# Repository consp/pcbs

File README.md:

This repository contains most of my public available PCB designs. Some are also in other repo's since they need software with them.

Available:

* SOJ32 <-> DIP32s adapter for SRAM chips
* MIDI Adapter for 15 pin gameport ports
* Adapter board for Sparta ION XGT motors

Not publicly available/on request:

* 3 PORT USB <-> CAN adapter compatible with custom linux socketcan kernel driver and modified SavvyCAN. https://github.com/consp/SavvyCAN
* Custom board for https://github.com/consp/ZigbeeP1

All stuff not already licenced otherwise (like forks) are only available under CC-BY-NC-4.0 https://creativecommons.org/licenses/by-nc/4.0/ . For commercial use contact me.

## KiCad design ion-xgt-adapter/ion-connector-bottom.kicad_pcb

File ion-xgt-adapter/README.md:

# Adapter for the (Sparta) ION XGT motors

The motor is a 20 pole, 24 slot PMSM. It should be able to function with hall sensors but due to how it's configured you need to make sure the hall sensors are very precicely aligned.
The top cover has a magnet ring which also has 20 magnet poles, we use that for hall sensors.

I forgot to take pictures before I sealed the motor again ... so no live images.

Features:
* WAGO 238-402 connector, which you can get from the original board
* Phoenix (or equivalen) 2.54mm screw terminals for the signal wires.
* Bottom and top traces for the phases since the cheap PCB manufacturers use 1oz copper you need as much as you can get, but it should be more than enough for the 24A max rating of the WAGO connectors.
* 0603 capacitor slots for when the s/n ratio is too much due to bad cable shielding, if you get a 15khz signal the phases are messing with the hall sensors. By putting a 1nF cap on all sensor lines you can get rid of some of the 15khz noise. Add caps to the power line if those cause troubles, this was not needed for my setup.
* (optional) Hall mounting bracket to get the sensors in the right place and keep them there, they need to be mounted max 9mm above the pcb. https://github.com/consp/cad/tree/master/sparta-ion-motor-hall

Advise to put together:

* Disassemble motor, and remove old PCBs
* Put new PCB in, make sure the contact is good with the phase screws. Middle screws can be ommitted, they are for tightening the fets to the heatsink but we do not need that but it's nice to have.
* Pull your favourite 8/9 strand wire though the bearing hole. If you remove the bearing from the coverplate and only install that, it is very easy to access.
* Put the phase leads into the connectors.
* Put the bearing in place, grease/seal the cable in place to avoid basic water ingress and put the bearing in the correct spot.
* Put on the cover plate and align the plate.
* Test the motor's functionality.
* It is possibley the hall phases are not exactly 60 degrees between transisions. You will need a motor controler which can handle that. They are consistent though.
* Seal the cover plate with anti-water sealant and tighten it.

# License

This work is licensed under CC BY-NC 4.0 (https://creativecommons.org/licenses/by-nc/4.0/)

# board

# Final version

# In the motor

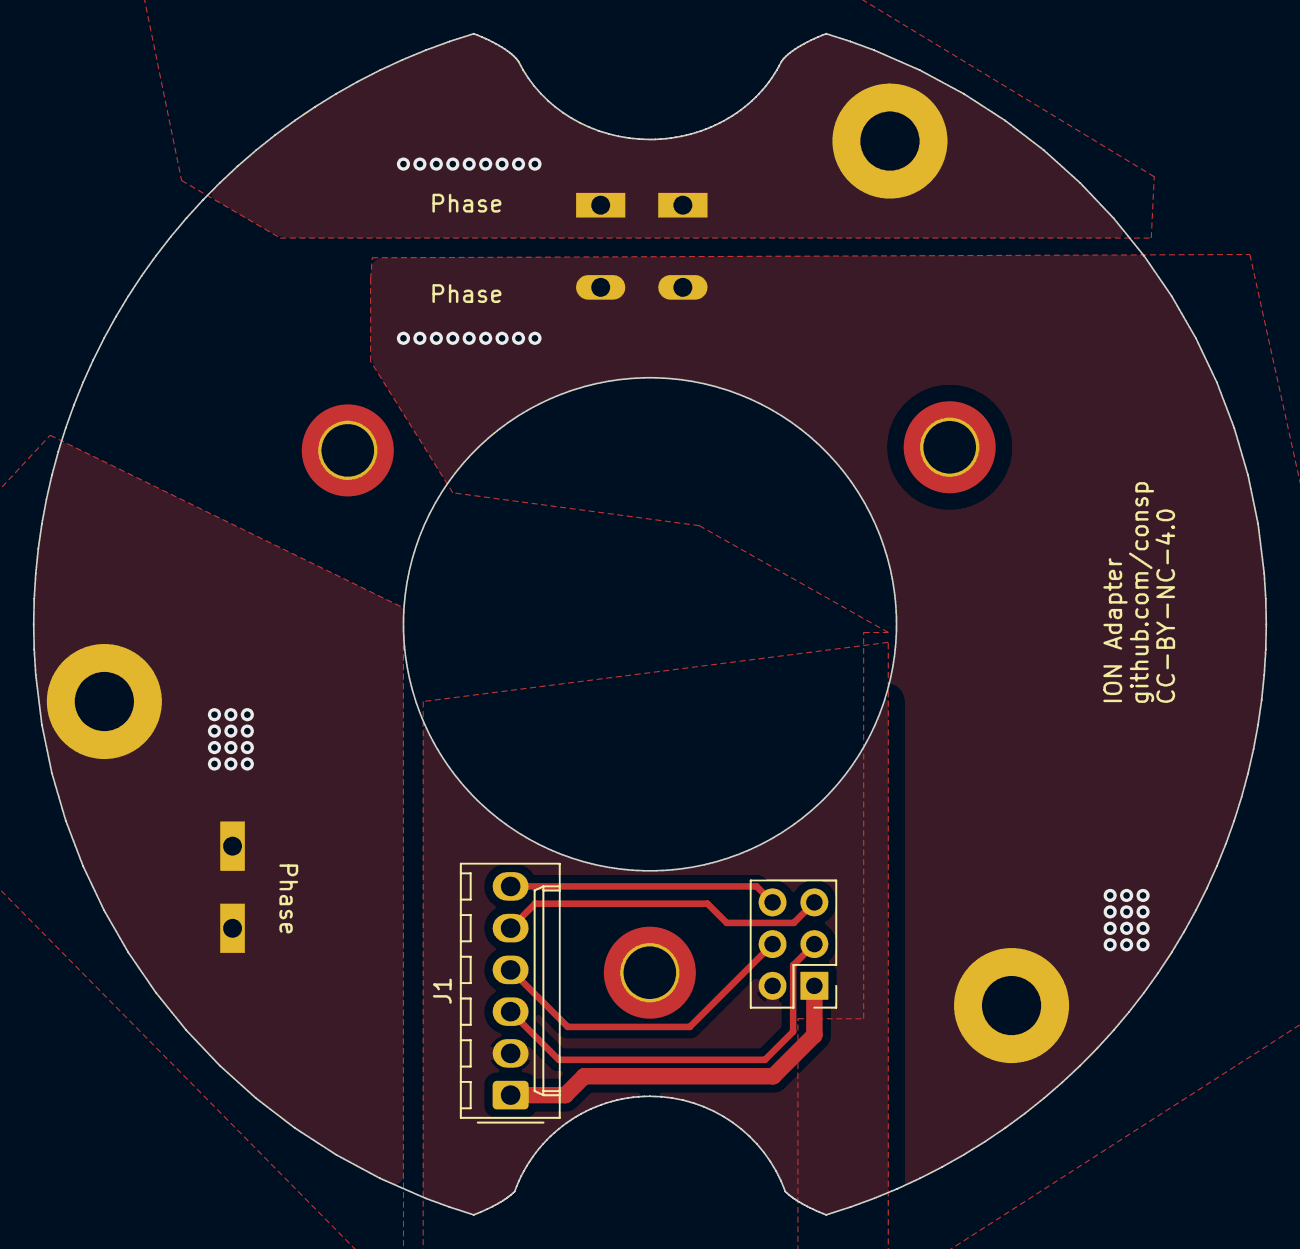
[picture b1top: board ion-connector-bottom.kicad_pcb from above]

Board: 2 copper layers, 75.0 x 71.9 mm, 10 parts (0 on the bottom side), 9 nets.

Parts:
B2B1: Conn_02x03_Odd_Even; PinHeader_2x03_P2.54mm_Vertical
H1, H2, H3: MountingHole_Pad; MountingHole_3.6mm_M3_DIN965_Pad
H4, H5, H6: MountingHole; MountingHole_3.2mm_M3_DIN965_Pad_TopBottom
J1: Conn_01x06; Molex_KK-254_AE-6410-06A_1x06_P2.54mm_Vertical
J2: Conn_01x01; TerminalBlock_WAGO_236-401_1x01_P5.00mm_45Degree
Ph1: Conn_01x02; TerminalBlock_WAGO_236-402_1x02_P5.00mm_45Degree

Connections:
+5V: B2B1.1, J1.1
/B: H2.1, Ph1.2
/G: H3.1, J2.1
/HB: B2B1.5, J1.5
/HG: B2B1.3, J1.3
/HY: B2B1.4, J1.4
/TEMP: B2B1.6, J1.6
/Y: H1.1, Ph1.1
GND: B2B1.2, J1.2

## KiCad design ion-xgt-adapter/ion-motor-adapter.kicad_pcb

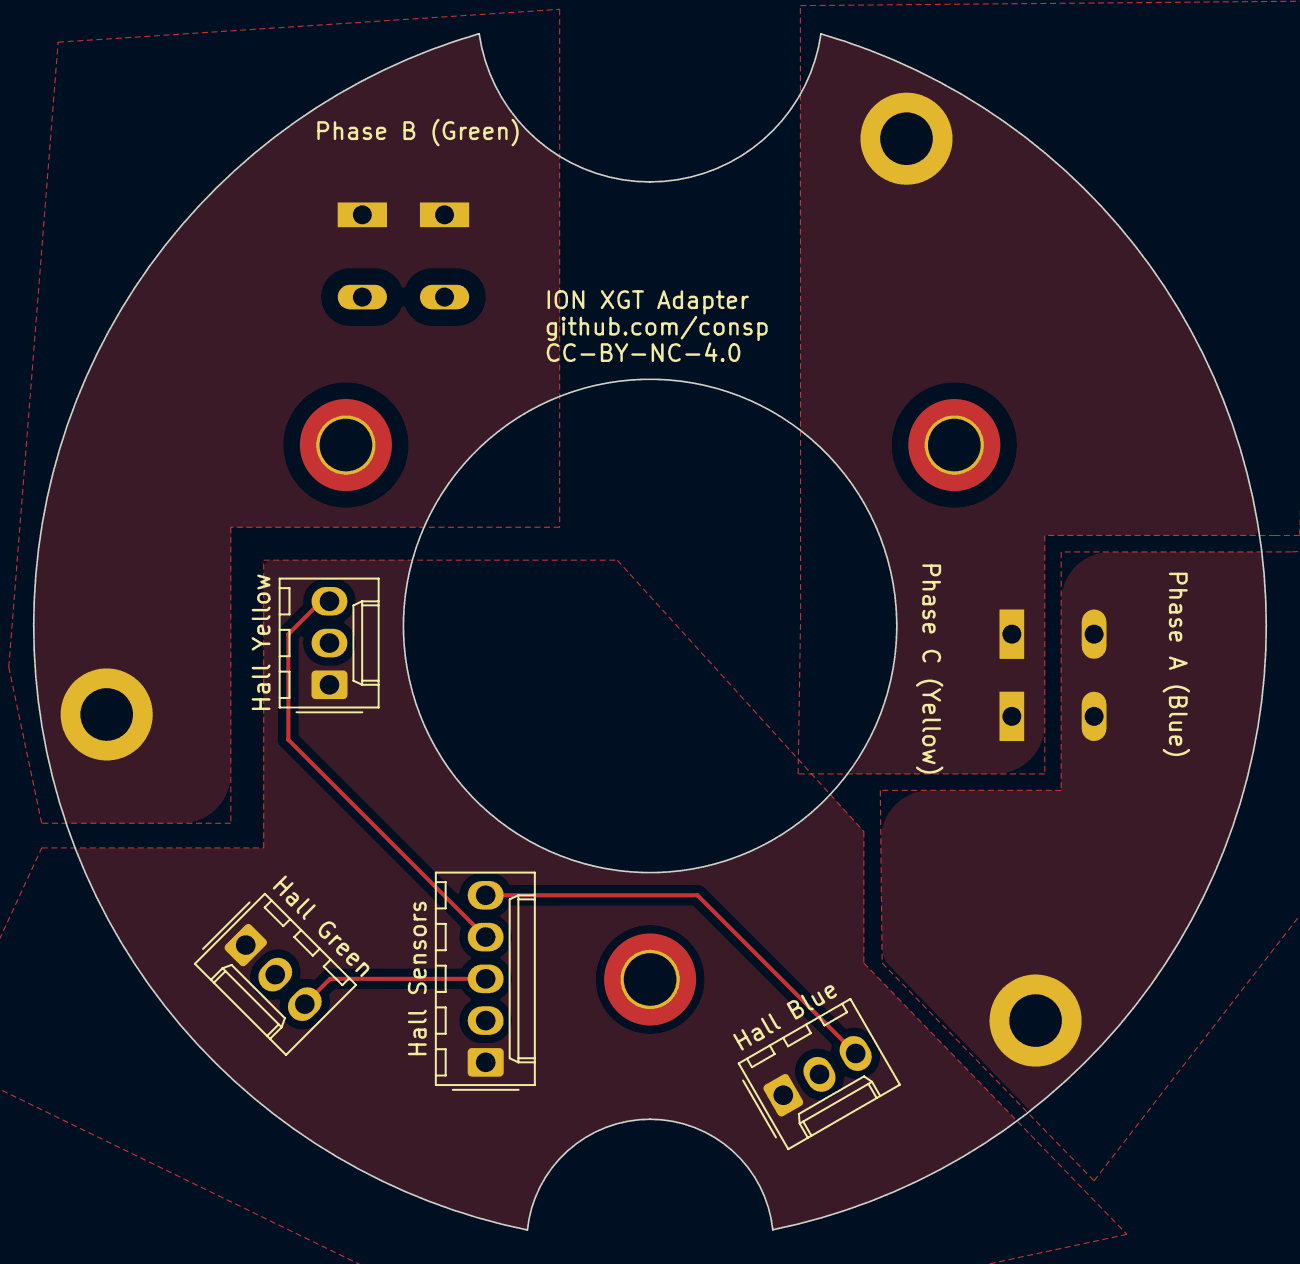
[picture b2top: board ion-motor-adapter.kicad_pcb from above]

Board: 2 copper layers, 75.0 x 72.8 mm, 12 parts (0 on the bottom side), 8 nets.

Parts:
H1, H2, H3: MountingHole_Pad; MountingHole_3.2mm_M3_DIN965_Pad
H4, H5, H6: MountingHole; MountingHole_3.2mm_M3_DIN965_Pad_TopBottom
Hall Blue: Conn_01x03; Molex_KK-254_AE-6410-03A_1x03_P2.54mm_Vertical
Hall Green: Conn_01x03; Molex_KK-254_AE-6410-03A_1x03_P2.54mm_Vertical
Hall Sensors: Conn_01x05; Molex_KK-254_AE-6410-05A_1x05_P2.54mm_Vertical
Hall Yellow: Conn_01x03; Molex_KK-254_AE-6410-03A_1x03_P2.54mm_Vertical
PhG1: Conn_01x02; TerminalBlock_WAGO_236-402_1x02_P5.00mm_45Degree
PhYB1: Conn_01x02; TerminalBlock_WAGO_236-402_1x02_P5.00mm_45Degree

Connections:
+5V: Hall Blue.1, Hall Green.1, Hall Sensors.1, Hall Yellow.1
/B: H2.1, PhYB1.2
/G: H3.1, PhG1.1
/Y: H1.1, PhYB1.1
GND: Hall Blue.2, Hall Green.2, Hall Sensors.2, Hall Yellow.2
unnamed: Hall Green.3, Hall Sensors.3
unnamed: Hall Sensors.4, Hall Yellow.3
unnamed: Hall Blue.3, Hall Sensors.5

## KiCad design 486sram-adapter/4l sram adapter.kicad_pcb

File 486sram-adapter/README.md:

# SOJ32 <-> DIP32s adapter

These files contain an adapter allowing you to use a SOJ32 package SRAM chip on older 486 (and other) motherboards. Some others have been posted on vogons but I could not find any available schematics so I made another one inspired by some of those available on the forum.

This pcb is 4 layered, if you want the 2 layered version contact me. I also have a TSOP version but that one is not finished and untested.

# How to

Solder the SOJ32/28 chip by means available to you, if you do it like me it might get messy but it will work. 

* SOJ32: solder as is
* SOJ28: solder on the lower pins, optionally cut the top of the board off to make it fit

Noteworthy parts:

* CE and VDD are connected. All motherboards I have already do this and I have never seen one with a different variant, they all use OE to enable them. 
* The pads near pin 3 can be used for a 0603 diode to drop the voltage to allow 4.5v chips to be used since they have ~.5v tollerance on the input pins. YMMV since it will still be out of spec of the chips. Make sure you carefully select a diode as the voltage drop is dependant on current. Make sure to cut the strip connecting the pads if you intend to do this.
* The pads near the SOJ32 part can be used for an optional 0805 capacitor, value at your chosing.
* To connect the pins, cut the middle ones a bit short and solder everything together. It should hold up just fine especially if you use a strip of them. It is recommended to use the thinner pin-arrays but as you can see below I did not have those available and standard 2.54mm pins might work on your motherboard.
* Impedence was not calculated for the board design so YMMV in that respect. I'm not versed in those black arts and had to accept the Apple developer agreement in the past, so my soul cannot be sold again to acquire those.

# How it looks

Note: wire to hold it on an angle is not included.

# License

This work is licensed under CC BY-NC 4.0 (https://creativecommons.org/licenses/by-nc/4.0/)

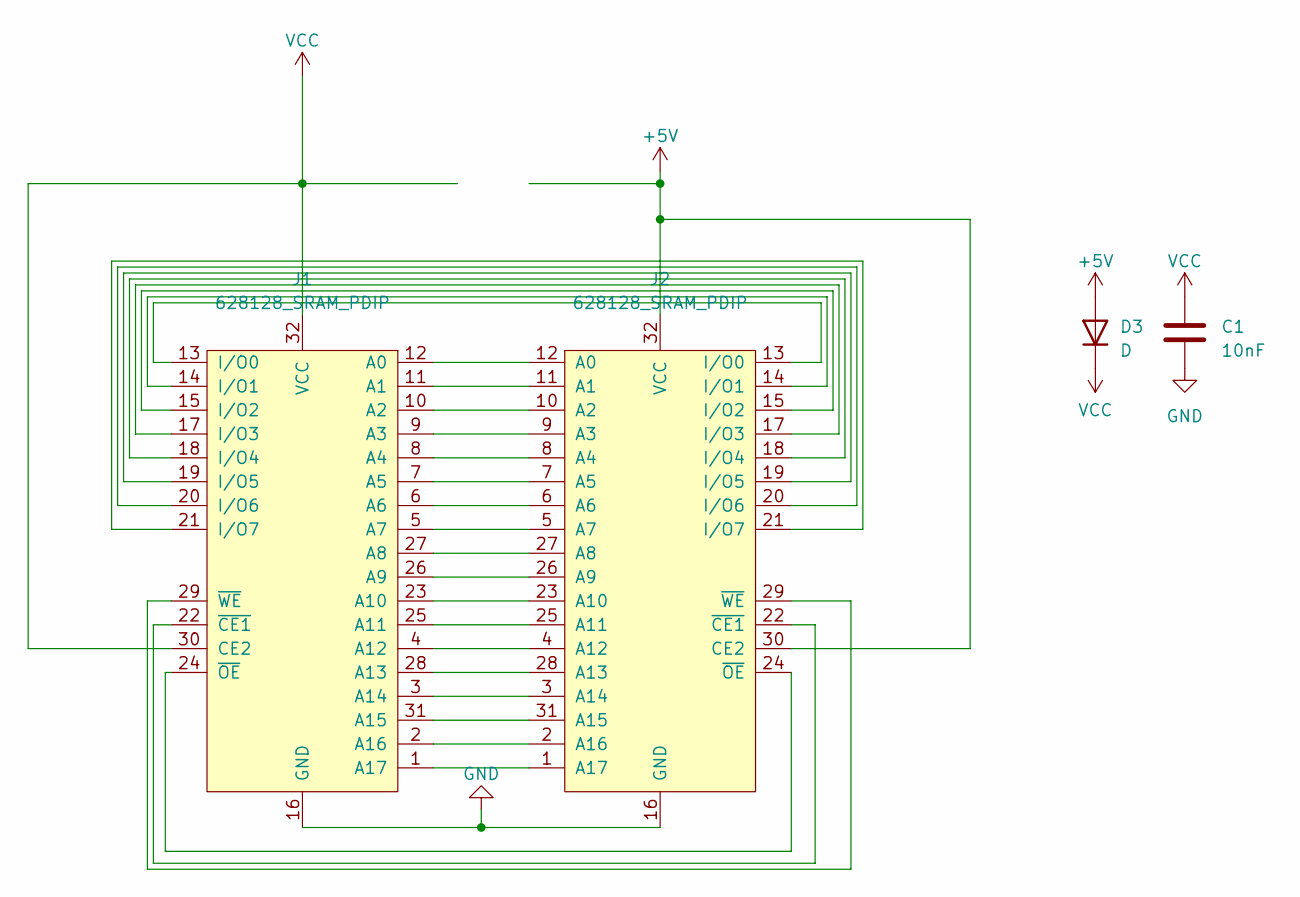
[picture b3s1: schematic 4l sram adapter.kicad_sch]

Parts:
C1: 10nF; C_0805_2012Metric_Pad1.18x1.45mm_HandSolder
D3: D; D_0603_1608Metric_Pad1.05x0.95mm_HandSolder
J1: 628128_SRAM_PDIP; SOJ-32
J2: 628128_SRAM_PDIP; PDIP-32-Special

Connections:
+5V: D3.2 (A), J2.30 (CE2), J2.32 (VCC)
GND: C1.2, J1.16 (GND), J2.16 (GND)
unnamed: J1.12 (A0), J2.12 (A0)
unnamed: J1.11 (A1), J2.11 (A1)
unnamed: J1.10 (A2), J2.10 (A2)
unnamed: J1.9 (A3), J2.9 (A3)
unnamed: J1.8 (A4), J2.8 (A4)
unnamed: J1.7 (A5), J2.7 (A5)
unnamed: J1.6 (A6), J2.6 (A6)
unnamed: J1.5 (A7), J2.5 (A7)
unnamed: J1.27 (A8), J2.27 (A8)
unnamed: J1.26 (A9), J2.26 (A9)
unnamed: J1.23 (A10), J2.23 (A10)
unnamed: J1.25 (A11), J2.25 (A11)
unnamed: J1.4 (A12), J2.4 (A12)
unnamed: J1.28 (A13), J2.28 (A13)
unnamed: J1.3 (A14), J2.3 (A14)
unnamed: J1.31 (A15), J2.31 (A15)
unnamed: J1.2 (A16), J2.2 (A16)
unnamed: J1.1 (A17), J2.1 (A17)
unnamed: J1.13 (I/O0), J2.13 (I/O0)
unnamed: J1.14 (I/O1), J2.14 (I/O1)
unnamed: J1.15 (I/O2), J2.15 (I/O2)
unnamed: J1.17 (I/O3), J2.17 (I/O3)
unnamed: J1.18 (I/O4), J2.18 (I/O4)
unnamed: J1.19 (I/O5), J2.19 (I/O5)
unnamed: J1.20 (I/O6), J2.20 (I/O6)
unnamed: J1.21 (I/O7), J2.21 (I/O7)
unnamed: J1.22 (~CE1), J2.22 (~CE1)
unnamed: J1.24 (~OE), J2.24 (~OE)
unnamed: J1.29 (~WE), J2.29 (~WE)
VCC: C1.1, D3.1 (K), J1.30 (CE2), J1.32 (VCC)

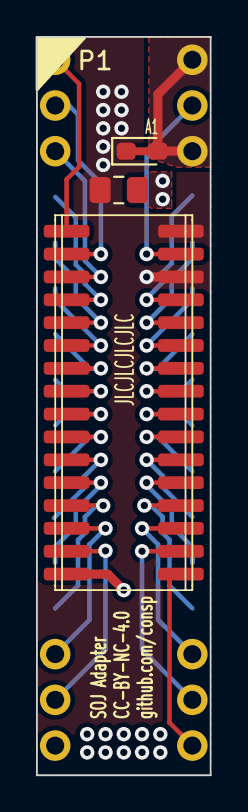
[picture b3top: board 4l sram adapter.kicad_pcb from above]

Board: 4 copper layers, 9.7 x 41.0 mm, 4 parts (0 on the bottom side), 32 nets.

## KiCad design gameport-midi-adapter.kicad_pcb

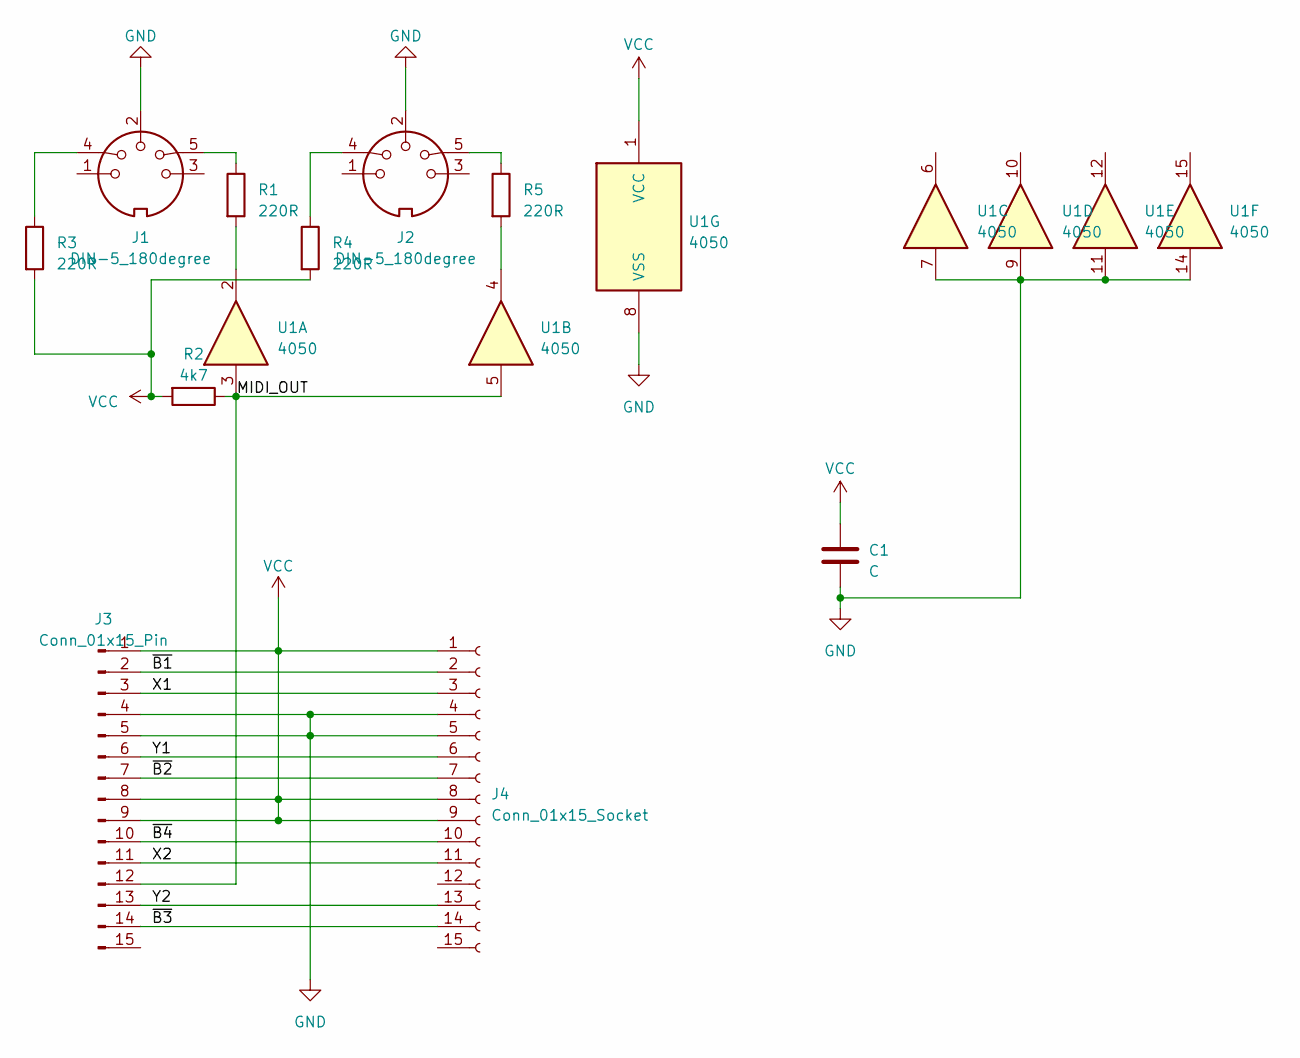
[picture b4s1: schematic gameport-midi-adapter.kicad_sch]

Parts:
C1: C; CP_Radial_Tantal_D4.5mm_P5.00mm
J1, J2: DIN-5_180degree; MIDI_DIN5
J3: Conn_01x15_Pin; DSUB-15_Male_Horizontal_P2.77x2.84mm_EdgePinOffset7.70mm_Ho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
J4: Conn_01x15_Socket; DSUB-15_Female_Horizontal_P2.77x2.84mm_EdgePinOffset7.70mm_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
R1, R3, R4, R5: 220R; R_Axial_DIN0207_L6.3mm_D2.5mm_P10.16mm_Horizontal
R2: 4k7; R_Axial_DIN0207_L6.3mm_D2.5mm_P10.16mm_Horizontal
U1: 4050; DIP-16_W7.62mm

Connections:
/MIDI_OUT: J3.12, R2.1, U1.3, U1.5
/X1: J3.3, J4.3
/X2: J3.11, J4.11
/Y1: J3.6, J4.6
/Y2: J3.13, J4.13
/~B1: J3.2, J4.2
/~B2: J3.7, J4.7
/~B3: J3.14, J4.14
/~B4: J3.10, J4.10
GND: C1.2, J1.2, J2.2, J3.4, J3.5, J4.4, J4.5, U1.7, U1.8 (VSS), U1.9, U1.11, U1.14
unnamed: J1.4, R3.1
unnamed: J1.5, R1.1
unnamed: J2.4, R4.1
unnamed: J2.5, R5.1
unnamed: R1.2, U1.2
unnamed: R5.2, U1.4
VCC: C1.1, J3.1, J3.8, J3.9, J4.1, J4.8, J4.9, R2.2, R3.2, R4.2, U1.1 (VCC)

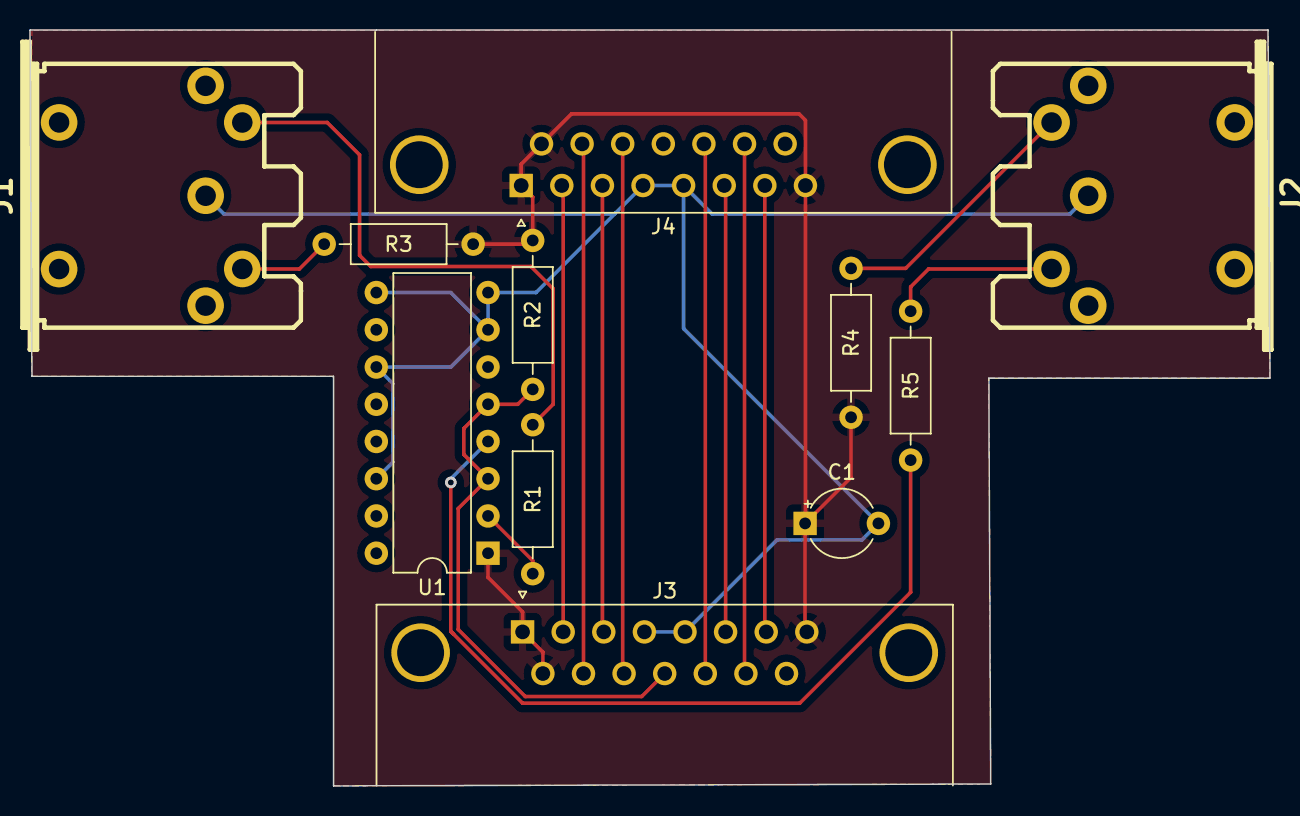
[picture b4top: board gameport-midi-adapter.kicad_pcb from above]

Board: 2 copper layers, 84.6 x 51.6 mm, 11 parts (0 on the bottom side), 17 nets.

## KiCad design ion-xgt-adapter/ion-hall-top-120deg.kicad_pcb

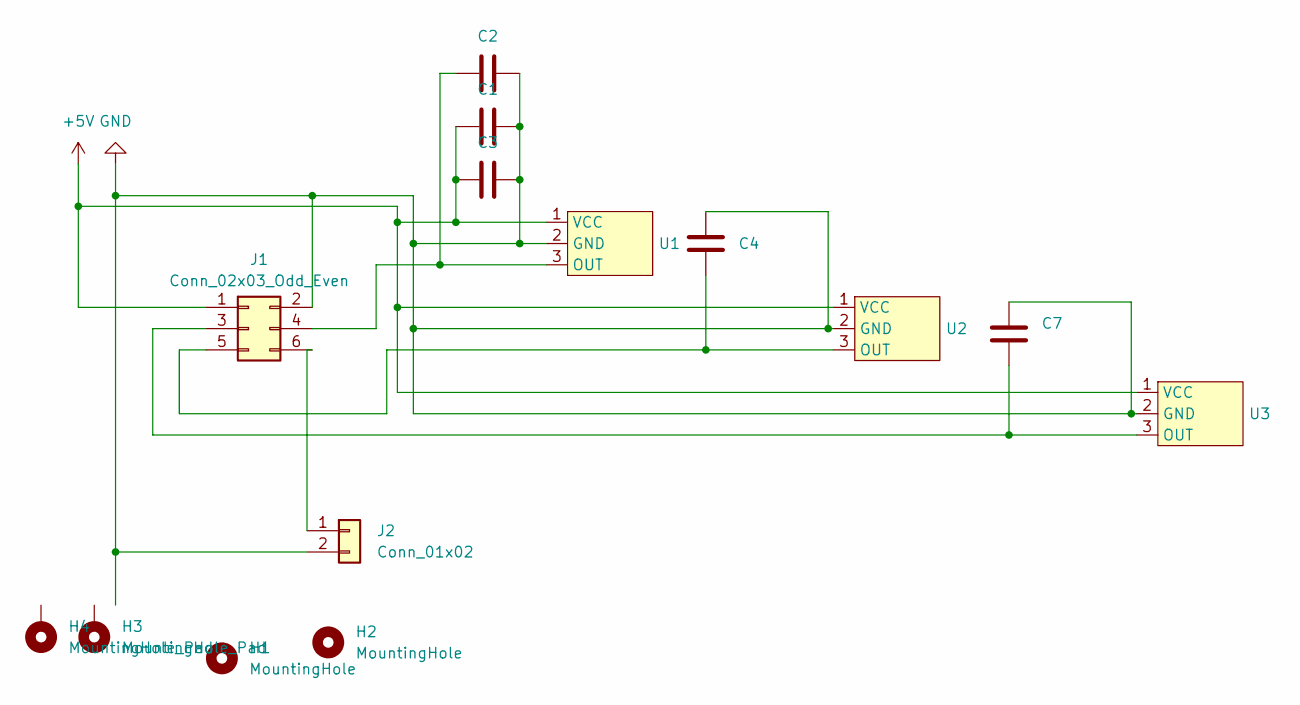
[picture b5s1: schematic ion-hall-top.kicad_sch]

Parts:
C1, C2, C3, C4: C_0603_1608Metric_Pad1.08x0.95mm_HandSolder
C7: 10nF; C_0603_1608Metric_Pad1.08x0.95mm_HandSolder
H1, H2: MountingHole; MountingHole_2.1mm
H3, H4: MountingHole_Pad; MountingHole_3.2mm_M3_Pad
J1: Conn_02x03_Odd_Even; PinSocket_2x03_P2.54mm_Vertical
J2: Conn_01x02; SolderWire-0.25sqmm_1x02_P4.2mm_D0.65mm_OD1.7mm
U1, U2, U3: TO-92_Inline_30mm_offset

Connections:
+5V: C1.2, C3.2, J1.1, U1.1 (VCC), U2.1 (VCC), U3.1 (VCC)
GND: C1.1, C2.1, C3.1, C4.1, C7.1, J1.2, J2.2, U1.2 (GND), U2.2 (GND), U3.2 (GND)
unnamed: C7.2, J1.3, U3.3 (OUT)
unnamed: C2.2, J1.4, U1.3 (OUT)
unnamed: C4.2, J1.5, U2.3 (OUT)
unnamed: J1.6, J2.1

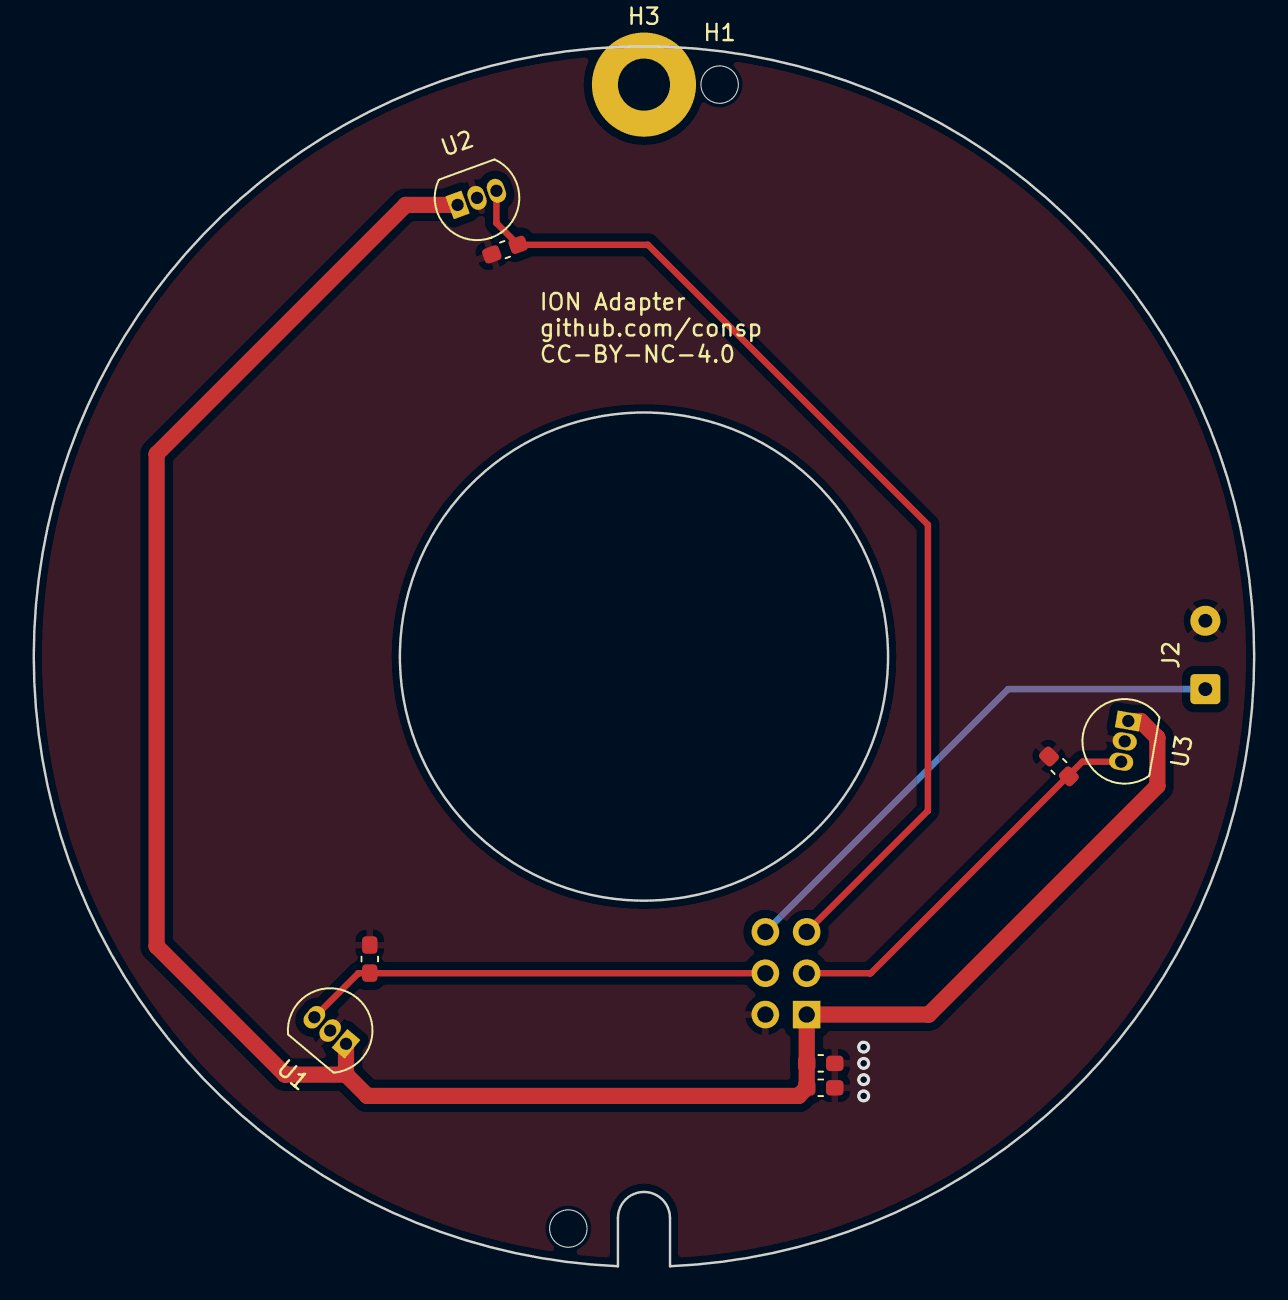
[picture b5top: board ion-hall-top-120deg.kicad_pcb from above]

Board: 2 copper layers, 75.0 x 75.0 mm, 13 parts (1 on the bottom side), 6 nets.

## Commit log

2023-11-11 Commit of files, readme and license.
2023-11-11 Fixed oversized image.
2024-01-12 Moved files
2024-01-12 Added soj32 adapter
2024-01-12 Added Main README and updated gameport adapter
2024-01-12 Update README.md to fix image
2024-01-12 Update README.md to pins
2024-01-12 Update README.md wrt impedance
2024-01-14 Added initial version of XGT Adapter board
2024-01-14 added image
2024-01-14 Cleared up readme. i was still sleepy
2024-02-27 Working version
2025-01-15 Add in-place images
2025-01-15 Added images to readme
